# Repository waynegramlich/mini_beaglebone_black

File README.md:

mini_beaglebone_black
=====================

BeagleBone Black Mini Shield to bridge between a
BeagleBone Black and a BusDuino.

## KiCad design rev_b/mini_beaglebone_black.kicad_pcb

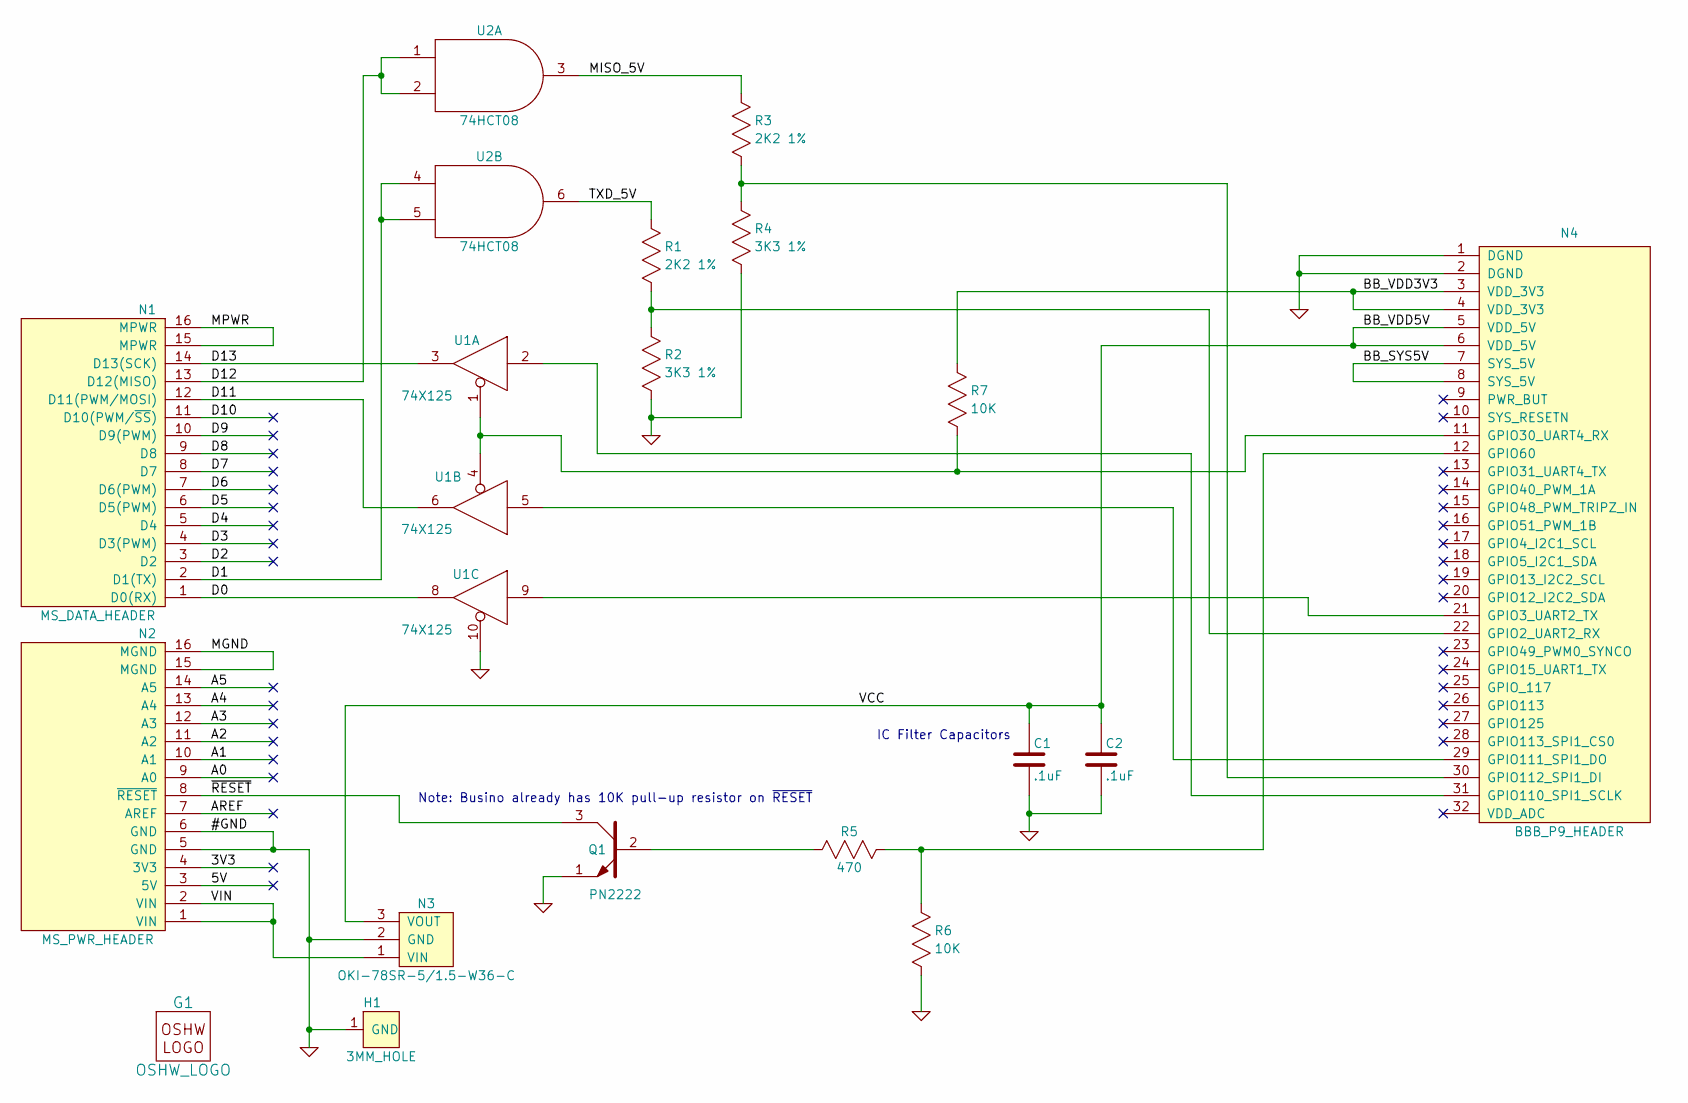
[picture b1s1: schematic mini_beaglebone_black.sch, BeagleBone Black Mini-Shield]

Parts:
C1, C2: .1uF
G1: OSHW_LOGO
H1: 3MM_HOLE
N1: MS_DATA_HEADER
N2: MS_PWR_HEADER
N3: OKI-78SR-5/1.5-W36-C
N4: BBB_P9_HEADER
Q1: PN2222
R1, R3: 2K2 1%
R2, R4: 3K3 1%
R5: 470
R6, R7: 10K
U1: 74X125
U2: 74HCT08

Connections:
/3V3: N2.4 (3V3)
/5V: N2.3 (5V)
/A0: N2.9 (A0)
/A1: N2.10 (A1)
/A2: N2.11 (A2)
/A3: N2.12 (A3)
/A4: N2.13 (A4)
/A5: N2.14 (A5)
/AREF: N2.7 (AREF)
/BB_SYS5V: N4.7 (SYS_5V), N4.8 (SYS_5V)
/BB_VDD3V3: N4.3 (VDD_3V3), N4.4 (VDD_3V3), R7.2
/D0: N1.1 (D0(RX)), U1.8
/D1: N1.2 (D1(TX)), U2.4, U2.5
/D2: N1.3 (D2)
/D3: N1.4 (D3(PWM))
/D4: N1.5 (D4)
/D5: N1.6 (D5(PWM))
/D6: N1.7 (D6(PWM))
/D7: N1.8 (D7)
/D8: N1.9 (D8)
/D9: N1.10 (D9(PWM))
/D10: N1.11 (D10(PWM/~SS))
/D11: N1.12 (D11(PWM/MOSI)), U1.6
/D12: N1.13 (D12(MISO)), U2.1, U2.2
/D13: N1.14 (D13(SCK)), U1.3
/MGND: N2.15 (MGND), N2.16 (MGND)
/MISO_5V: R3.2, U2.3
/MPWR: N1.15 (MPWR), N1.16 (MPWR)
/TXD_5V: R1.2, U2.6
/VIN: N2.1 (VIN), N2.2 (VIN), N3.1 (VIN)
/~RESET: N2.8 (~RESET), Q1.3
GND: C1.2, C2.2, H1.1, N2.5 (GND), N2.6 (GND), N3.2 (GND), N4.1 (DGND), N4.2 (DGND), Q1.1, R2.1, R4.1, R6.1, U1.7 (GND), U1.10, U2.7 (GND)
unnamed: N4.11 (GPIO30_UART4_RX), R7.1, U1.1, U1.4
unnamed: N4.12 (GPIO60), R5.2, R6.2
unnamed: N4.21 (GPIO3_UART2_TX), U1.9
unnamed: N4.22 (GPIO2_UART2_RX), R1.1, R2.2
unnamed: N4.29 (GPIO111_SPI1_DO), U1.5
unnamed: N4.30 (GPIO112_SPI1_DI), R3.1, R4.2
unnamed: N4.31 (GPIO110_SPI1_SCLK), U1.2
unnamed: Q1.2, R5.1
VCC: C1.1, C2.1, N3.3 (VOUT), N4.5 (VDD_5V), N4.6 (VDD_5V), U1.14 (VCC), U2.14 (VCC)

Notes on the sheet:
Note: Busino already has 10K pull-up resistor on ~RESET
IC Filter Capacitors

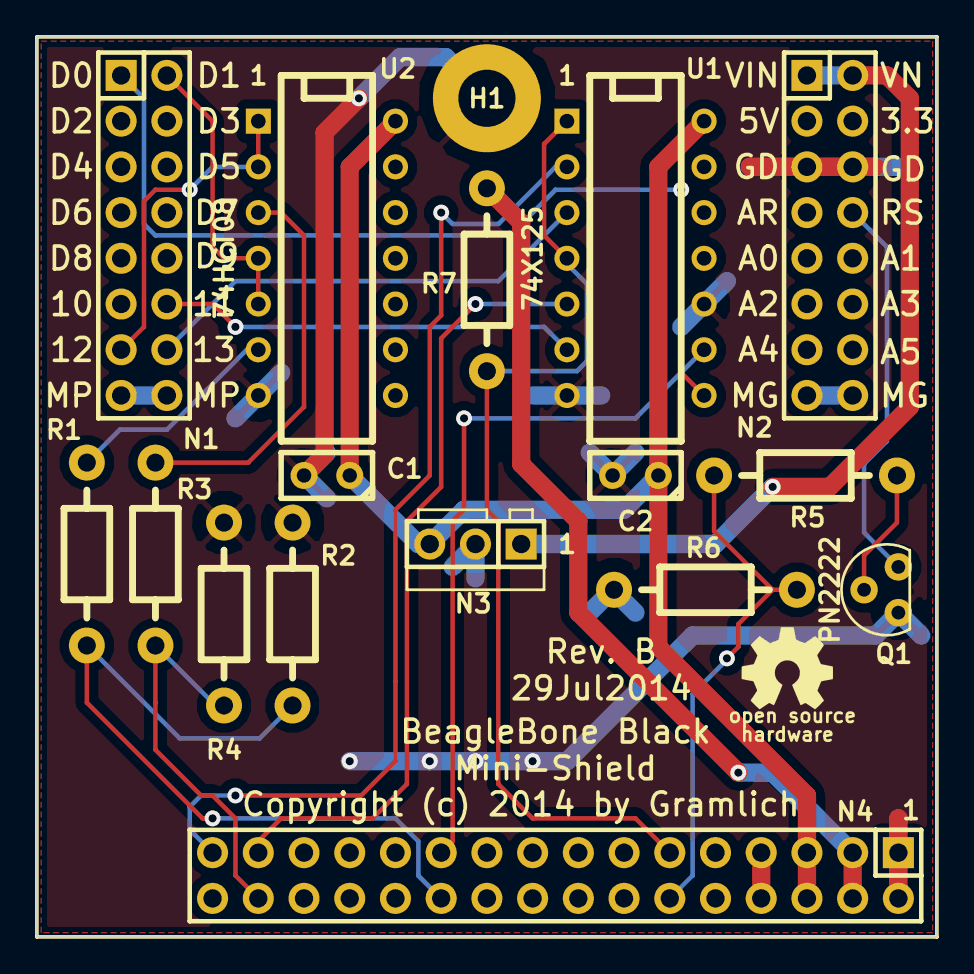
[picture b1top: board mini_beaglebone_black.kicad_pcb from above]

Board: 2 copper layers, 50.0 x 50.0 mm, 18 parts (0 on the bottom side), 23 nets.

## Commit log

2014-07-05 Performed initial copy of Template Mini-Shield.
2014-07-07 Got first layout of BBB Mini-Shield done.
2014-07-12 Did another polishing sweep through the board.
2014-07-13 Added Edge Cuts.
2014-07-13 Moved one trace too close too PCB edge.
2014-07-28 Made a clone of Rev. A
2014-07-29 Cloned rev_a to rev_b.
2014-07-29 Moved R3 and R4

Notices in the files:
rev_b/mini_beaglebone_black.kicad_pcb:
Copyright (c) 2014 by Gramlich
Copyright (c)
